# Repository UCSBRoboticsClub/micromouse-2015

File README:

CONTRIBUTORS
Austin
Gauthier
Charles
Patrick
Tirion
Nickolas

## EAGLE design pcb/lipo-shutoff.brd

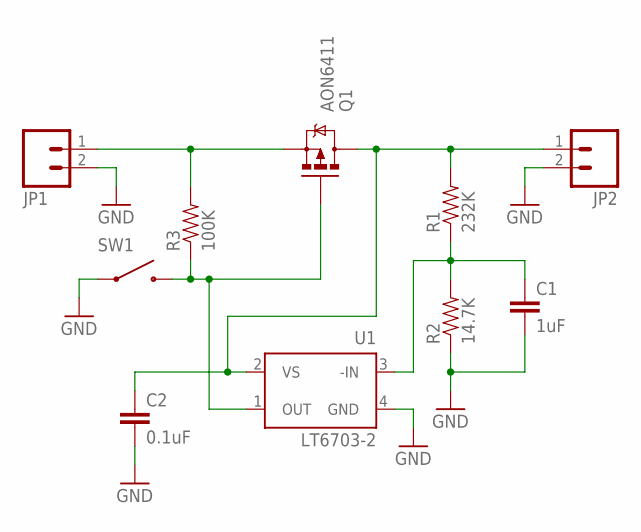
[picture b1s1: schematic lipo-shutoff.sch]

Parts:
C1: 1uF; 0603-CAP
C2: 0.1uF; 0603-CAP
JP1, JP2: M02LOCK_LONGPADS; 1X02_LOCK_LONGPADS
Q1: AON6411; DFN5X6
R1: 232K; 0603-RES
R2: 14.7K; 0603-RES
R3: 100K; 0603-RES
SW1: FSM4JSMA
U1: LT6703-2; LT6703

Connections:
GND: C1.2, C2.2, JP1.2, JP2.2, R2.1, SW1.1, SW1.2 (1), U1.4 (GND)
unnamed: JP1.1, Q1.1 (S), Q1.2 (S), Q1.3 (S), R3.2
unnamed: Q1.4 (G), R3.1, SW1.3 (2), SW1.4 (2), U1.1 (OUT)
unnamed: C2.1, JP2.1, Q1.5 (D), Q1.6 (D), Q1.7 (D), Q1.8 (D), Q1.PAD (D), R1.2, U1.2 (VS)
unnamed: C1.1, R1.1, R2.2, U1.3 (-IN)

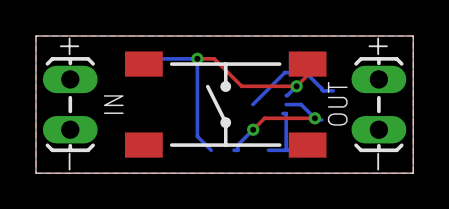
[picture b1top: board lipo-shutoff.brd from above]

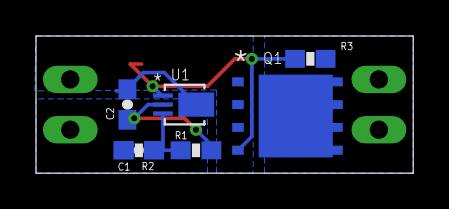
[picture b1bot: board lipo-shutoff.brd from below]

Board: 2 copper layers, 21.0 x 7.6 mm, 10 parts (7 on the bottom side), 5 nets.

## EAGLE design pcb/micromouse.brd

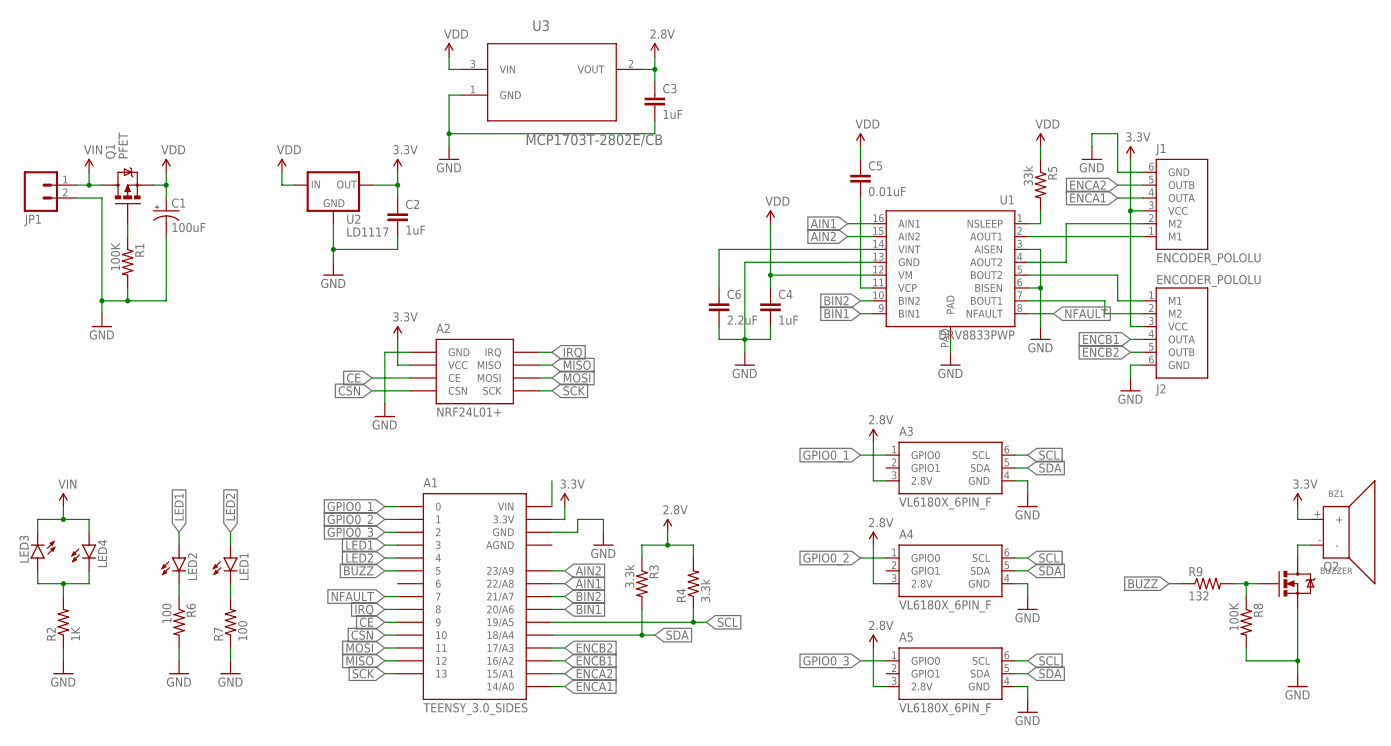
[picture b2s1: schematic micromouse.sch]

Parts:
A1: TEENSY_3.0_SIDES
A2: NRF24L01+
A3, A4, A5: VL6180X_6PIN_F; 2X3HEADER
BZ1: BUZZER
C1: 100uF; CPOL-RADIAL-100UF-25V
C2, C3, C4: 1uF; 0603-CAP
C5: 0.01uF; 0603-CAP
C6: 2.2uF; 0603-CAP
J1, J2: ENCODER_POLOLU; 1XM06-LOCK
JP1: M02LOCK_LONGPADS; 1X02_LOCK_LONGPADS
LED1, LED2, LED3, LED4: LED0603; LED-0603
Q1: PFET; SOT23-3
Q2: MOSFET-NCHANNELBSS123LT1G; SOT23-3
R1, R8: 100K; 0603-RES
R2: 1K; 0603-RES
R3, R4: 3.3k; 0603-RES
R5: 33k; 0603-RES
R6, R7: 100; 0603-RES
R9: 132; 0603-RES
U1: DRV8833PWP; HTSSOP-16
U2: LD1117; SOT-223
U3: MCP1703T-2802E/CB; SOT95P300X145-3N

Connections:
2.8V: A3.3 (2.8V), A4.3 (2.8V), A5.3 (2.8V), C3.1, R3.1, R4.2, U3.2 (VOUT)
3.3V: A1.3.3V, A2.2 (VCC), BZ1.+, C2.1, J1.3 (VCC), J2.3 (VCC), U2.2 (OUT), U2.4 (OUT)
AGND: A1.AGND
AIN1: A1.22/A8, U1.16 (AIN1)
AIN2: A1.23/A9, U1.15 (AIN2)
BIN1: A1.20/A6, U1.9 (BIN1)
BIN2: A1.21/A7, U1.10 (BIN2)
BUZZ: A1.5, R9.1
CE: A1.9, A2.3 (CE)
CSN: A1.10, A2.4 (CSN)
ENCA1: A1.14/A0, J1.4 (OUTA)
ENCA2: A1.15/A1, J1.5 (OUTB)
ENCB1: A1.16/A2, J2.4 (OUTA)
ENCB2: A1.17/A3, J2.5 (OUTB)
GND: A1.GND, A2.1 (GND), A3.4 (GND), A4.4 (GND), A5.4 (GND), C1.2 (-), C2.2, C3.2, C4.2, C6.2, J1.6 (GND), J2.6 (GND), JP1.2, Q2.2 (S), R1.2, R2.1, R6.2, R7.1, R8.2, U1.3 (AISEN), U1.6 (BISEN), U1.13 (GND), U1.PAD, U2.1 (GND), U3.1 (GND)
GPIO0_1: A1.0, A3.1 (GPIO0)
GPIO0_2: A1.1, A4.1 (GPIO0)
GPIO0_3: A1.2, A5.1 (GPIO0)
IRQ: A1.8, A2.8 (IRQ)
LED1: A1.3, LED2.A
LED2: A1.4, LED1.A
MISO: A1.12, A2.7 (MISO)
MOSI: A1.11, A2.6 (MOSI)
unnamed: Q1.1 (G), R1.1
unnamed: LED3.A, LED4.C, R2.2
unnamed: J1.1 (M1), U1.2 (AOUT1)
unnamed: LED2.C, R6.1
unnamed: J1.2 (M2), U1.4 (AOUT2)
unnamed: J2.1 (M1), U1.5 (BOUT2)
unnamed: BZ1.-, Q2.3 (D)
unnamed: J2.2 (M2), U1.7 (BOUT1)
unnamed: R5.2, U1.1 (NSLEEP)
unnamed: C6.1, U1.14 (VINT)
unnamed: C5.2, U1.11 (VCP)
unnamed: LED1.C, R7.2
unnamed: Q2.1 (G), R8.1, R9.2
NFAULT: A1.7, U1.8 (NFAULT)
SCK: A1.13, A2.5 (SCK)
SCL: A1.19/A5, A3.6 (SCL), A4.6 (SCL), A5.6 (SCL), R4.1
SDA: A1.18/A4, A3.5 (SDA), A4.5 (SDA), A5.5 (SDA), R3.2
VDD: C1.1 (+), C4.1, C5.1, Q1.2 (S), R5.1, U1.12 (VM), U2.3 (IN), U3.3 (VIN)
VIN: JP1.1, LED3.C, LED4.A, Q1.3 (D)

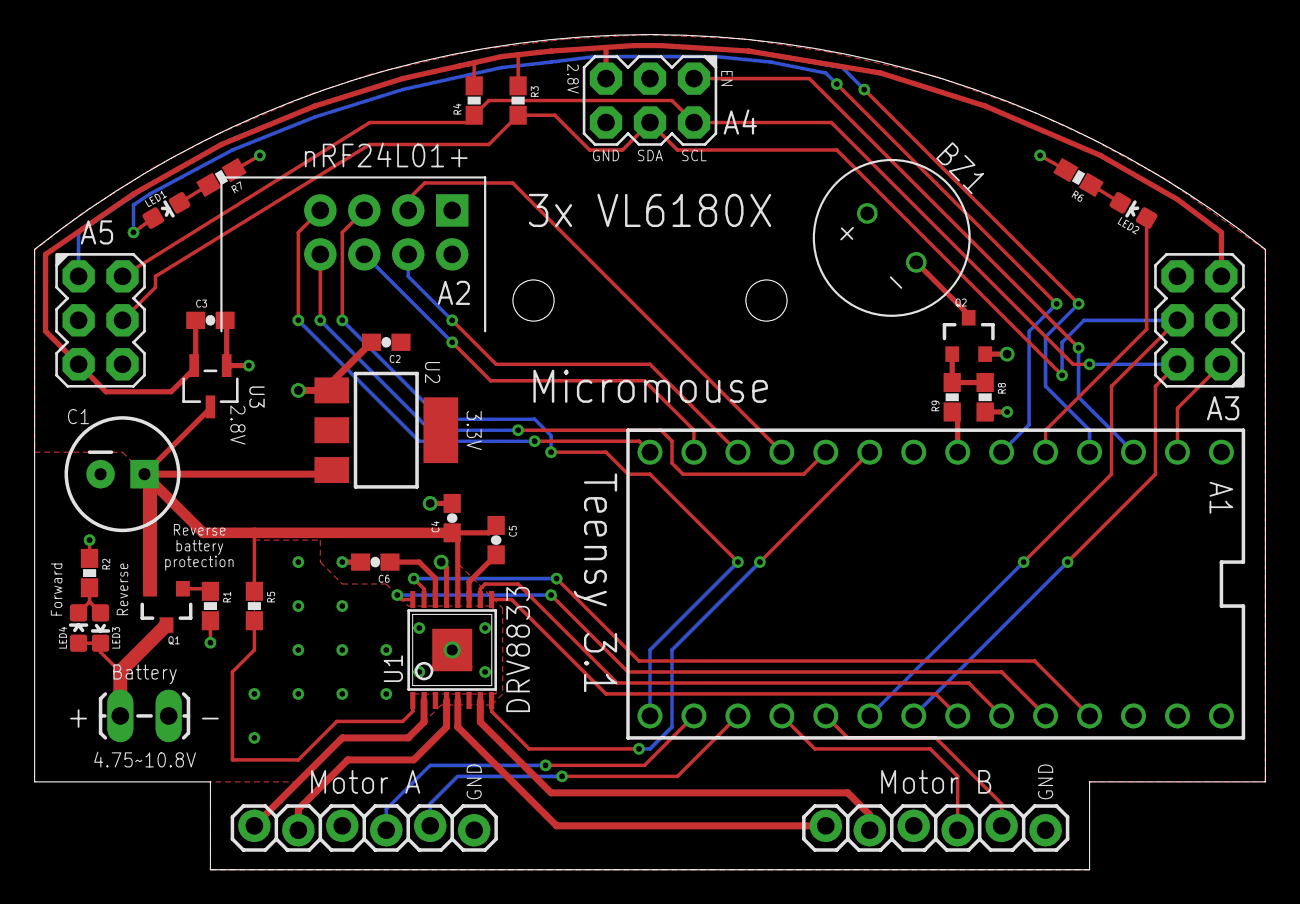
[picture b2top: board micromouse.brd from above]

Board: 2 copper layers, 71.1 x 48.3 mm, 33 parts (0 on the bottom side), 41 nets.

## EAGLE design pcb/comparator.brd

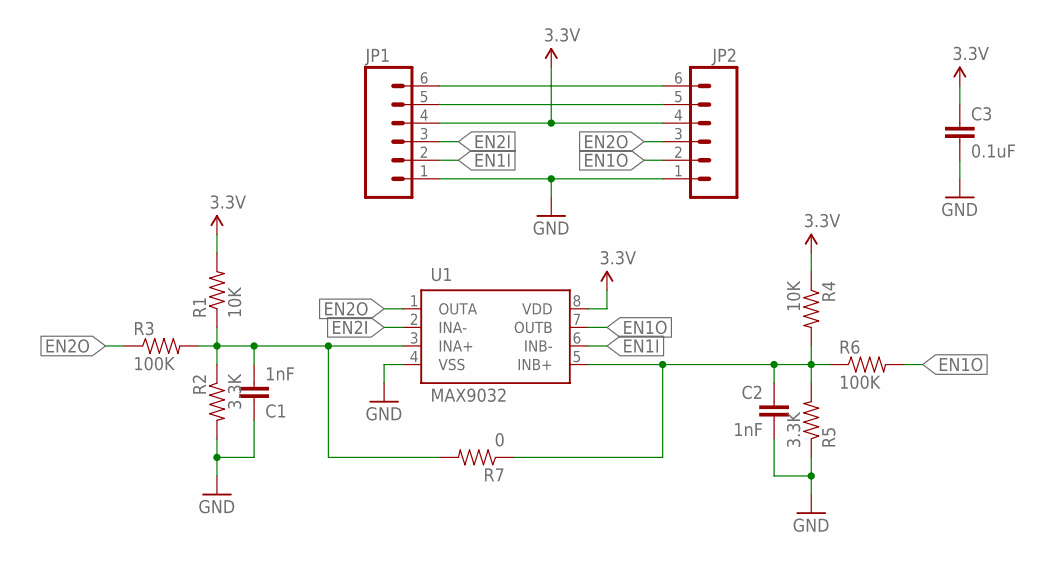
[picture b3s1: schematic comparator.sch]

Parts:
C1, C2: 1nF; 0603-CAP
C3: 0.1uF; 0603-CAP
JP1: M06SMDF; 1X06-SMD-FEMALE
JP2: M06LOCK; 1X06_LOCK
R1, R4: 10K; 0603-RES
R2, R5: 3.3K; 0603-RES
R3, R6: 100K; 0603-RES
R7: 0; 0603-RES
U1: MAX9032; SOT23-8

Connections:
3.3V: C3.1, JP1.4, JP2.4, R1.2, R4.1, U1.8 (VDD)
EN1I: JP1.2, U1.6 (INB-)
EN1O: JP2.2, R6.2, U1.7 (OUTB)
EN2I: JP1.3, U1.2 (INA-)
EN2O: JP2.3, R3.1, U1.1 (OUTA)
GND: C1.1, C2.2, C3.2, JP1.1, JP2.1, R2.2, R5.1, U1.4 (VSS)
unnamed: JP1.6, JP2.6
unnamed: JP1.5, JP2.5
unnamed: C1.2, R1.1, R2.1, R3.2, R7.2, U1.3 (INA+)
unnamed: C2.1, R4.2, R5.2, R6.1, R7.1, U1.5 (INB+)

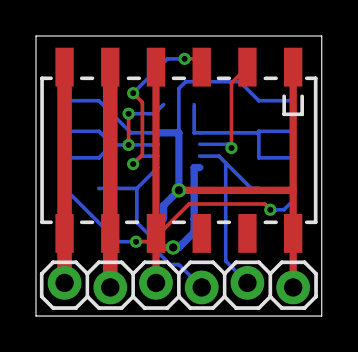
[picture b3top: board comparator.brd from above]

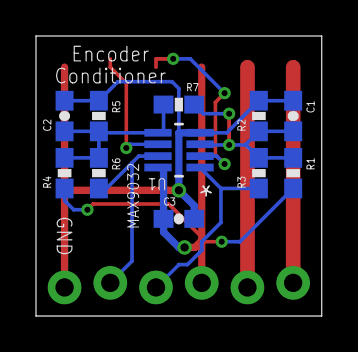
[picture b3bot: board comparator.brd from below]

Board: 2 copper layers, 15.9 x 15.6 mm, 13 parts (11 on the bottom side), 10 nets.

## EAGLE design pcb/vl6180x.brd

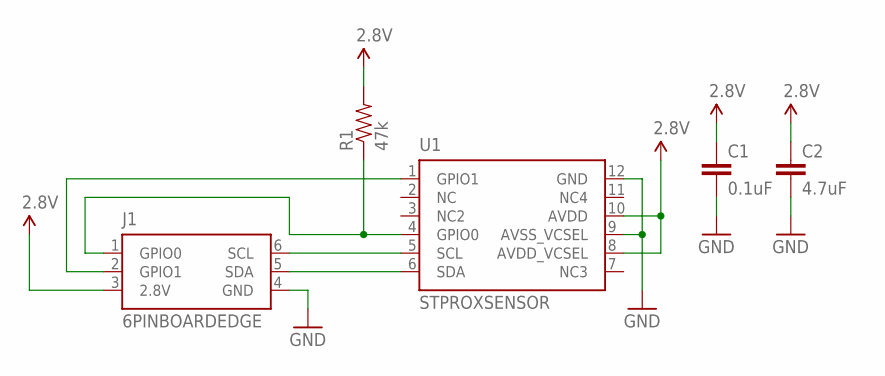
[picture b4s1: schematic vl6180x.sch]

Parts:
C1: 0.1uF; 0603-CAP
C2: 4.7uF; 0603-CAP
J1: 6PINBOARDEDGE
R1: 47k; 0603-RES
U1: STPROXSENSOR

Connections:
2.8V: C1.1, C2.1, J1.3 (2.8V), R1.2, U1.8 (AVDD_VCSEL), U1.10 (AVDD)
GND: C1.2, C2.2, J1.4 (GND), U1.9 (AVSS_VCSEL), U1.12 (GND)
unnamed: J1.1 (GPIO0), R1.1, U1.4 (GPIO0)
unnamed: J1.6 (SCL), U1.5 (SCL)
unnamed: J1.5 (SDA), U1.6 (SDA)
unnamed: J1.2 (GPIO1), U1.1 (GPIO1)

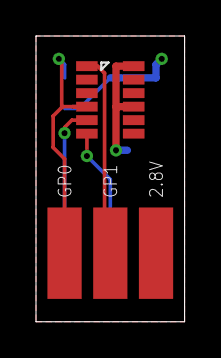
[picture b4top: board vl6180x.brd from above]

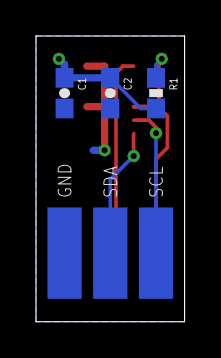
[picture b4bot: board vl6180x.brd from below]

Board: 2 copper layers, 8.3 x 15.9 mm, 5 parts (3 on the bottom side), 6 nets.

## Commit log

2015-01-23 added the code for micromouse
2015-01-23 created list of contributors
2015-02-07 Added micromouse pcb schematic
2015-02-07 Added distance sensor schematics and board designs
2015-02-07 Added pin labels to proximity sensor board
2015-02-07 Made labels bigger
2015-02-07 Added datasheets
2015-02-15 Added micromouse pcb layout
2015-02-16 Added buzzer
2015-02-16 Improved buzzer drive circuitry
2015-02-16 Added encoder comparator board
2015-02-16 Tweaked encoder conditiner board
2015-02-16 Added MAX9032 datasheet
2015-03-02 Fixed 2.8v regulator pinout
2015-03-04 Changed led resistors
2015-03-05 Ported over code from 2014 repository, added music playing through buzzer
2015-03-05 Added test code for mouse sensor
2015-03-06 Specified capacitor value on comparator boards
2015-03-06 Tuned velocity loop
2015-03-07 Fixed and cleaned up code
2015-03-07 Added range sensor app note
2015-03-07 Fixed nsleep signal on board
2015-03-07 Fixed build errors and warnings
2015-03-07 Basic terminal functionality works
2015-03-07 Variable watching works
2015-03-07 Command prompt now lists valid commands when an invalid command is entered
2015-03-07 Setting variables through the terminal works
2015-03-07 Terminal command editing is nicer
2015-03-07 Added parameter print command
2015-03-07 Disables radio communcation if radio is not present
2015-03-08 Added mortal kombat theme song
2015-03-08 Updated recorder song
2015-03-08 Uses digitalWriteFast in most places
2015-03-08 Added BFS and maze files -- requires teensyduino 1.21
2015-03-09 Test BFS performance -- ~2us worst case
2015-03-09 Added battery protection board
2015-03-13 Added controller rx back to radio code
2015-03-14 Renamed ControlLoop and added radio controller support
2015-03-14 mm.cpp
    some copy pastable code for orientation and position
2015-03-14 Fixed music playback
2015-03-14 Variable setting over the terminal is more versatile
2015-03-15 Added micromouse motion planning simulation
2015-03-15 Improved simulation accuracy
2015-03-15 Added convenience macros for command lists
2015-03-15 Fixed syntax error
2015-03-15 Added derivative term, made error modeling more accurate
2015-03-17 Fixed filter constant calculation in simulation
2015-04-23 Added position tracking using encoders
2015-04-23 Added line needed for float printf on newer teensyduino versions
2015-04-25 Implemented state correction using distance sensors
2015-04-25 Fixed state correction
2015-04-27 Follows walls
2015-04-28 Added ability to save a log of variables
2015-04-28 Motion planning works better
2015-04-28 Fixed radio communication
2015-04-29 Motion is less erratic when near the target
2015-04-29 Wall following works better
2015-05-03 Fixed lipo cutoff board
2015-05-03 Fixed a few things
2015-05-04 Navigates to target cell
2015-05-04 No longer have to call writeLog() in the main loop
2015-05-04 Basic maze solving implemented
2015-05-05 Added maze printout
2015-05-05 Fixed indentation
2015-05-05 Fixed some motion planning bugs
2015-05-05 Front sensor determines whether wall is in this cell or next
2015-05-05 Fixed last commit
2015-05-06 Solves maze
2015-05-07 Solves maze faster
2015-05-08 Speeds up after each run
2015-05-09 Inproved perfmormance near target
2015-05-09 Button board works
2015-05-09 Switch 1 disables filling in maze walls
2015-05-09 Press button 1 to abort run and restart at start cell
2015-05-10 Can increase speed after resetting
2015-05-16 Friday

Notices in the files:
parts and their libraries:
SparkFun-Connectors: Licensing: Creative Commons ShareAlike 4.0 International - https://creativecommons.org/licenses/by-sa/4.0
